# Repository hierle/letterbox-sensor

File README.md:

# LoRaWan EU868MHz Letterbox Sensor

New version letterbox sensor v2 available here: https://github.com/hierle/letterbox-sensor-v2 :)

sensing letters in your letterbox via IR diode pair, sending out status via LoRaWan/TTN
based on Attiny84, RFM95W, HSDL9100, powered by a CR2032 battery.

This is basically a clone of the heise ct briefkasten sensor project<br> 
https://www.heise.de/ratgeber/IoT-Netz-LoRaWAN-Briefkastensensor-mit-hoher-Reichweite-selber-bauen-4417179.html<br>
https://github.com/jamct/radio-mailbox

Contents:
- ./PCB/ :               kicad PCB files
- ./calibrate/ :         calibration sketch to adjust the poti for letter distance
- ./letterbox_sensor/ :  lora letterbox sensor sketch
- ./misc/ :              payload decoder, sample http integration cgi

Compiled with platformio, hex flashed to attiny with ArduinoISP

Changes:
- created SMD PCB
- onboard 868MHz PCB antenna after TI document http://www.ti.com/lit/an/swra227e/swra227e.pdf
- switched MISO/MOSI lines of RFM95
- Attiny pin renumbering 0...10 -> 10...0
- sensor pin naming changed from 8 -> A2, otherwise no ADC reading
- added basic temperature reading from RFM95
- added sensor raw value, voltage, temperature in lora package

BOM (digikey.de):

|Part number        |  Description            |
|-------------------|-------------------------|
|ATTINY84A-SSUR     |  IC MCU 8BIT 14SOIC     |
|HSDL-9100-021      |  PROXIMITY SENSOR       |
|RFM95W-868S2       |  RF TXRX MODULE         |
|3314G-1-105E       |  TRIMMER 1M OHM         |
|BU2032SM-FH-GTR    |  CR2032 COIN CELL HOLDER|
|HLE-103-02-L-DV    |  CONN RCPT 6POS         |
|AA3528LSECKT/J4    |  LED ORANGE             |
|CRGCQ1206F33R      |  33R 1206               |
|CRGCQ1206F220R     |  220R 1206              |
|LQG18HN1N8S00D     |  IND 1.8NH 0603         |
|GRM1885C1H2R7CA01D |  CAP 2.7PF 0603         |

An extended web ui by Peter is available here: https://github.com/pbiering/letterbox-sensor-web

Have fun!

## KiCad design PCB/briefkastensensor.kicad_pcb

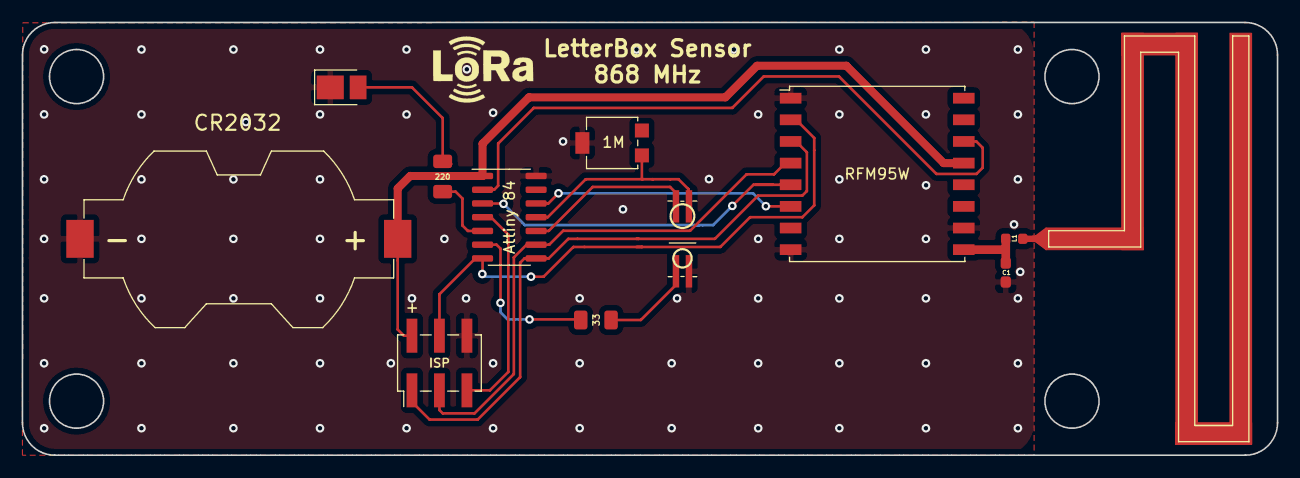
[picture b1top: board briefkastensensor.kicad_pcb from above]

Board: 2 copper layers, 116.0 x 40.0 mm, 12 parts (0 on the bottom side), 17 nets.

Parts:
AE1: Antenna; TI-DN024-SL-SHORT
Attiny 84: ATtiny84-20PU; SOIC-14_3.9x8.7mm_P1.27mm
C1: C_Small; C_0603_1608Metric_Pad1.05x0.95mm_HandSolder
CR2032: Conn_01x02; BatteryHolder_Keystone_1058_1x2032
D1: HSDL-9100-021; HSDL-9100
D2: LED; LED_PLCC_2835_Handsoldering
ISP: AVR-ISP-6; PinHeader_2x03_P2.54mm_Vertical_SMD
L1: L; L_0603_1608Metric
R1: 33; R_1206_3216Metric
R2: 220; R_1206_3216Metric
R3: 1M; Potentiometer_Bourns_3314G_Vertical
U2: RFM95W; HOPERF_RFM9XW_SMD

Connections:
+3V3: Attiny 84.1, CR2032.1, ISP.2, U2.13
GND: Attiny 84.14, C1.2, CR2032.2, D1.2, D2.1, ISP.6, R3.2, U2.1, U2.8, U2.10
MISO: Attiny 84.8, ISP.1, U2.3
MOSI: Attiny 84.7, ISP.4, U2.2
unnamed: AE1.1, L1.1
unnamed: C1.1, L1.2, U2.9
unnamed: D1.1, R1.2
unnamed: Attiny 84.11, D1.3, R3.1
unnamed: Attiny 84.10, D1.4
unnamed: D2.2, R2.2
unnamed: Attiny 84.6, R1.1
unnamed: Attiny 84.5, R2.1
unnamed: Attiny 84.2, U2.14
unnamed: Attiny 84.3, U2.5
unnamed: Attiny 84.12, U2.6
RST: Attiny 84.4, ISP.5
SCK: Attiny 84.9, ISP.3, U2.4

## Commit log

2019-10-22 letterbox sensor initial version
2019-10-22 readme added
2019-10-22 github release
2019-10-22 added kicad pcb
2019-10-22 added helper scripts
2019-10-25 added BOM
2019-10-30 beatified PCB image (thx Hotti)
2019-10-30 beautified PCB image (thx Hotti)
2019-11-01 initial fork
2019-11-04 add deltaLastChanged and threshold per dev_id in config
2019-11-04 change color in case lastReceived is above limits
2019-11-04 dump config options, extend whitelist for config chars
2019-11-04 bugfix
2019-11-07 fix+improve delta time calc+display
2019-11-10 add hooks for additional modules, minor reorg
2019-11-10 statistics module
2019-11-10 cosmetics
2019-11-10 add module prefix to functions and global variables
2019-11-10 inital version
2019-11-10 bugfix, add rrd module
2019-11-10 improve mobile scaling
2019-11-11 add support for snr/rssi
2019-11-11 add adjusted status filled/emptied also to content hash to be used by data update hooks
2019-11-11 change RRD font render mode
2019-11-11 add query string handling, add additional buttons for switching graphics on/off
2019-11-12 rework button implementation
2019-11-13 implement rrdRange support, adjust rrd database
2019-11-13 sync height of button
2019-11-13 implement auto-reload button
2019-11-14 change colors of rrdRange buttons, use different xgrid for mobile devices
2019-11-14 update doc
2019-11-14 add support for HTTP_TTN_LETTERBOX_QUERY_STRING (SSI/mod_include), change color of Reload button
2019-11-14 initial version
2019-11-15 remove border of RRD to get it smaller
2019-11-15 remove hour/days from receivedstatus graphics
2019-11-15 cosmetic name change
2019-11-16 improve filled/empty detection on initialization
2019-11-17 minor fixes/reorg
2019-11-17 bugfixes
2019-11-17 rename HTTP_TTN_LETTERBOX_QUERY_STRING to HTTP_X_TTN_LETTERBOX_QUERY_STRING
2019-11-17 ignore json
2019-11-17 improve debugging
2019-11-17 implement hooks for authentication, cosmetics, reorg
2019-11-18 honor time token from cookie, store expiry in auth cookie
2019-11-18 proper message for missing session auth cookie
2019-11-19 bugfix+start changepw implementation
2019-11-19 cosmetic improvements on pictures
2019-11-19 start implementing password change (still unfinished)
2019-11-19 fix html
2019-11-20 insert dev_id into pictures + timestamp
2019-11-21 minor bugfixes
2019-11-23 cosmetics, minor bugfixes
2019-11-23 add reset button add 2-bit option switch add resistor to trimmer
2019-11-23 change resistor from 10 to 1 k
2019-11-23 add comments
2019-11-26 add support for plain and json output
2019-12-14 add translation support for "de"
2019-12-14 add missing translation
2020-01-07 use only major language token for translation support
2020-02-13 improve layout for Mobile browers, fix RRD database definition to cover 1y instead of 12d
2020-02-13 improve layout for Mobile browers
2020-08-28 fix issues on EL8 and add various META HTTP-EQUIV to avoid local brower caching
2020-11-09 fix german translation
2020-11-09 reduce branch to misc only
2021-06-27 add simulator script
2021-06-27 add notification extension "Signal" via D-Bus
2021-06-27 fix copyright header
2021-06-27 expose language to modules
2021-06-27 add support for notifyDbusSignal
2021-06-27 update changelog
2021-06-27 add signal-cli hint
2021-06-27 catch notification sent status and log accordingly
2021-06-27 cosmetics for logging
2021-06-27 add mailbox icon
2021-06-28 honor debug=0
2021-06-28 add module and extended support for ttn-letterbox-notifyEmail.pm
2021-06-28 add example options
2021-06-28 do not log if not enabled and debug is not enabled
2021-08-20 log empty recipent list only on debug level
2021-10-01 adjust German translation
2021-10-30 add support for v3 API and change to default
2021-10-30 optionally overwrite decoded payload defaults by environment
2021-10-30 add support for v3 API
2021-10-30 add debugmask
2021-10-30 add some trace log
2021-10-30 add support for v3 API, extend debugging, add payload validator
2021-10-30 slightly adjusted payload formatter to work with v3
2021-10-30 whitespace fixes
2021-11-09 fix payload validator for "tempC" (supporting also negative values)
2022-02-17 fix "counter" related to v3 API
2022-02-17 add support for Salted Hash provided by Authen::Passphrase::SaltedDigest in case of Crypt::SaltedHash (only available on EPEL7) is not installed/available
2022-02-18 align config options, cosmetics
2022-02-18 align config options
2022-02-18 do not die in case of RRD updates happen too often
2022-02-18 undef debug option if disabled
2022-02-18 remove support of debug option by environment
2022-02-18 remove support of debug option by environment, align debug options
2022-02-18 add additional default config values
2022-02-18 add missing 'init_device' hook for POST
2022-02-18 add some debug lines
2022-02-18 add a comment
2022-02-19 display '*undef* in case a raw data value is missing (.e.g sometimes 'snr' for unknown reason)
2022-02-19 fix typo in changelog
2022-02-19 catch missing raw data entries and use "U" in RRD update
2022-02-19 fix typo in comment
2022-02-19 include device hash into module hook 'get_graphics' calls
2022-02-19 align prototyping for hook 'get_graphics'
2022-02-19 add additional graphics 'sensor-zoom-empty', insert sensor threshold line into graphics, code optimization
2022-03-23 add some WebUI screenshots
2022-03-24 unconditionally log initial creation of RRD file, change sequence of graphs
2022-03-24 update only information
2022-03-24 remove MIN/MAX from RRD because not used (saves disk space)
2022-03-24 unconditionally log initial creation of XPM files
2022-03-26 remove not implemented change from changelog
2022-03-26 adjust RRD definition (saves disk space)
2022-03-27 implement shift, prepare zoom
2022-03-27 initial implementation of zoom
2022-03-28 implement shift+zoom
2022-03-29 shift/zoom adjustments
2022-03-29 review shift/zoom
2022-03-29 change timestamp from UTC to localtime
2022-03-29 code cosmetics
2022-03-29 disable shift/zoom on mobile, move shift/zoom buttons
2022-03-31 define button height global, align button sizes
2022-03-31 align button sizes
2022-03-31 fix watermark on mobile
2022-03-31 fix comments
2022-04-02 add support for optional -E|-F <sensor>
2022-04-02 cosmetics, remove unused variable
2022-04-02 adjust/add comments, improve match
2022-04-02 adjust raw content in case of threshold is provided by config (fixes improper WebUI box status display)
2022-04-02 activate change of shift/zoom text color in case not default, remove eol code
2022-04-04 display RRDs for rssi, snr, voltage only in case of "details=on"
2022-04-04 add also tempC for details=on
2022-04-05 update comments
2022-04-05 code cosmetic
2022-04-05 display receivedstatus only in case of "details=on"
2022-04-05 'sensor-zoom-empty' only in case of "details=on"
2022-04-05 comment cosmetics
2022-04-05 slight color adjustment for +/-
2022-04-15 clarify handling of "details"
2022-04-15 add additional "details" level "l1" with limited display of details
2022-04-15 display RRDs for 'rssi', 'snr', 'tempC' only in case of "details" != "l1" || "off"
2022-04-17 extend query string=value pattern check
2022-04-18 select charset for form, add id
2022-04-18 cosmetics/module loader related
2022-04-18 make browser language accessable
2022-04-18 catch empty user/pass in POST request
2022-04-18 improve comments
2022-04-18 add CAPTCHA support for login
2022-04-18 initial version of a readme
2022-04-18 fix typo
2022-04-21 add forgotten changelog entry
2022-04-21 return earlier from init if not enabled
2022-04-21 extend log line about storage of autogenerated uuid
2022-04-22 add support for options (used for local testing/debugging)
2022-04-22 catch empty ScriptCode
2022-04-22 add comment
2022-04-22 feed cookies into captcha verification and align response
2022-04-22 enable flexible cookie value handling
2022-04-22 change do flexible per captcha service module load, mark existing services as "external"
2022-04-22 insert javascript only in case of external captcha service
2022-04-22 add internal captcha support
2022-04-24 move font attribute into internal captcha service
2022-04-24 split captcha verification code between internal and external
2022-04-24 adjust internal captcha generation
2022-04-24 extend default config with example
2022-04-24 unify error message to user
2022-04-24 set user/pass input field as required
2022-04-24 set captcha field as required
2022-04-24 delay response also in case of htpasswd file has major issue
2022-04-24 minor bugfix
2022-04-24 improve CAPTCHA error message
2022-04-24 improve CAPTCHA error message #2
2022-04-24 html fixes
2022-04-24 remove hardwired input field name for internal captcha
2022-04-24 increase captcha
2022-04-24 change login window to vertical layout in case of mobile browser detected
2022-04-24 bugfix for mobile layout
2022-04-24 clean query string from URI in response if refresh_delay is given (e.g. logout)
2022-04-24 display "session problem" to user
2022-04-24 enable "tainted" mode
2022-04-24 cosmetics related to button size
2022-04-24 cosmetics/cleanup
2022-04-24 tainted mode not working still :-(
2022-04-24 use hardcoded binary /usr/bin/dbus-send to avoid insecure $ENV{PATH} in tainted mode
2022-04-24 final fix for tainted mode
2022-04-24 final enable tainted mode
2022-04-25 missing update related to GD::SecurityImage
2023-09-23 set counter to 0 in case neither 'counter' nor 'f_cnt' is set
2024-01-08 advertising new version v2
2024-01-18 added link to Peters web gui
